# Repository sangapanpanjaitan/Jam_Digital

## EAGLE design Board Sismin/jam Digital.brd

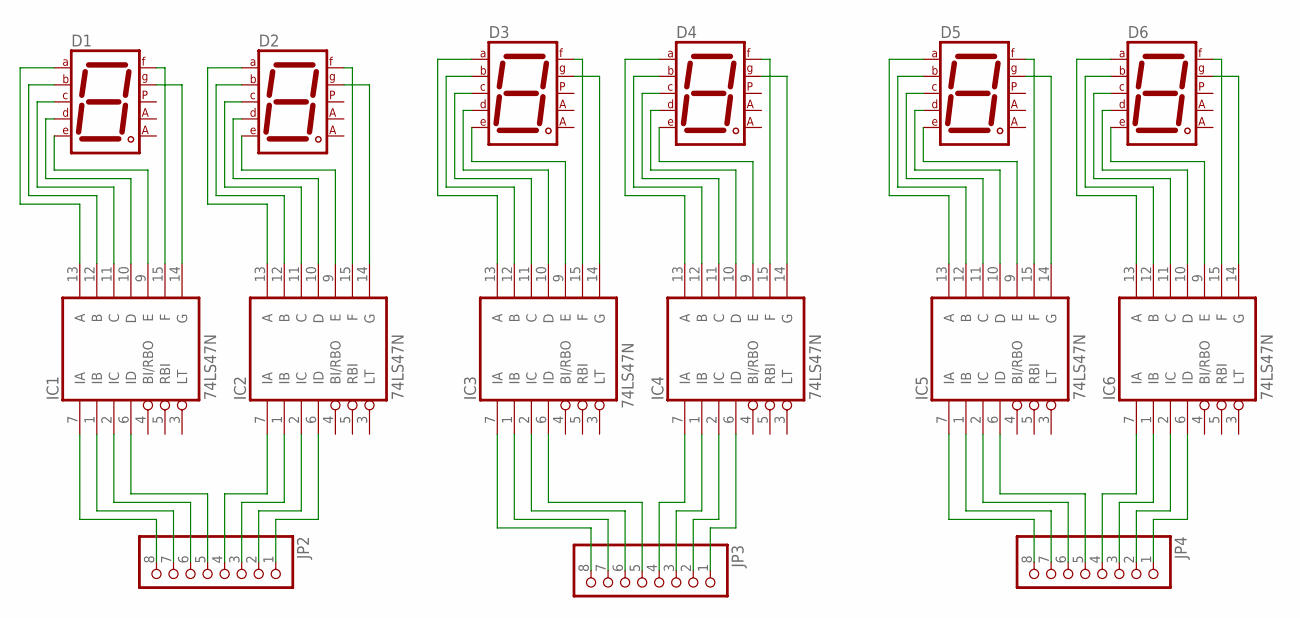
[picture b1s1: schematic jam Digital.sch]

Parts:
D1, D2, D3, D4, D5, D6: 7SEG-CA; 7SEG-13
IC1, IC2, IC3, IC4, IC5, IC6: 74LS47N; DIL16
JP2, JP3, JP4: PINHD-1X8; 1X08

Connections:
GND: IC1.8 (GND), IC2.8 (GND), IC3.8 (GND), IC4.8 (GND), IC5.8 (GND), IC6.8 (GND)
unnamed: D1.10 (G), IC1.14 (G)
unnamed: D2.10 (G), IC2.14 (G)
unnamed: D1.9 (F), IC1.15 (F)
unnamed: D2.9 (F), IC2.15 (F)
unnamed: D3.9 (F), IC3.15 (F)
unnamed: D3.10 (G), IC3.14 (G)
unnamed: D4.9 (F), IC4.15 (F)
unnamed: D4.10 (G), IC4.14 (G)
unnamed: D5.9 (F), IC5.15 (F)
unnamed: D5.10 (G), IC5.14 (G)
unnamed: D6.9 (F), IC6.15 (F)
unnamed: D6.10 (G), IC6.14 (G)
unnamed: D1.1 (E), IC1.9 (E)
unnamed: D1.2 (D), IC1.10 (D)
unnamed: D1.4 (C), IC1.11 (C)
unnamed: D1.6 (B), IC1.12 (B)
unnamed: D1.7 (A), IC1.13 (A)
unnamed: D2.1 (E), IC2.9 (E)
unnamed: D2.2 (D), IC2.10 (D)
unnamed: D2.4 (C), IC2.11 (C)
unnamed: D2.6 (B), IC2.12 (B)
unnamed: D2.7 (A), IC2.13 (A)
unnamed: D3.1 (E), IC3.9 (E)
unnamed: D3.2 (D), IC3.10 (D)
unnamed: D3.4 (C), IC3.11 (C)
unnamed: D3.6 (B), IC3.12 (B)
unnamed: D3.7 (A), IC3.13 (A)
unnamed: D4.1 (E), IC4.9 (E)
unnamed: D4.2 (D), IC4.10 (D)
unnamed: D4.4 (C), IC4.11 (C)
unnamed: D4.6 (B), IC4.12 (B)
unnamed: D4.7 (A), IC4.13 (A)
unnamed: D5.1 (E), IC5.9 (E)
unnamed: D5.2 (D), IC5.10 (D)
unnamed: D5.4 (C), IC5.11 (C)
unnamed: D5.6 (B), IC5.12 (B)
unnamed: D5.7 (A), IC5.13 (A)
unnamed: D6.1 (E), IC6.9 (E)
unnamed: D6.2 (D), IC6.10 (D)
unnamed: D6.4 (C), IC6.11 (C)
unnamed: D6.6 (B), IC6.12 (B)
unnamed: D6.7 (A), IC6.13 (A)
unnamed: IC1.7 (IA), JP2.8
unnamed: IC1.1 (IB), JP2.7
unnamed: IC1.2 (IC), JP2.6
unnamed: IC1.6 (ID), JP2.5
unnamed: IC2.7 (IA), JP2.4
unnamed: IC2.1 (IB), JP2.3
unnamed: IC2.2 (IC), JP2.2
unnamed: IC2.6 (ID), JP2.1
unnamed: IC3.7 (IA), JP3.8
unnamed: IC3.1 (IB), JP3.7
unnamed: IC3.2 (IC), JP3.6
unnamed: IC3.6 (ID), JP3.5
unnamed: IC4.7 (IA), JP3.4
unnamed: IC4.1 (IB), JP3.3
unnamed: IC4.2 (IC), JP3.2
unnamed: IC4.6 (ID), JP3.1
unnamed: IC5.7 (IA), JP4.8
unnamed: IC5.1 (IB), JP4.7
unnamed: IC5.2 (IC), JP4.6
unnamed: IC5.6 (ID), JP4.5
unnamed: IC6.7 (IA), JP4.4
unnamed: IC6.1 (IB), JP4.3
unnamed: IC6.2 (IC), JP4.2
unnamed: IC6.6 (ID), JP4.1
VCC: IC1.16 (VCC), IC2.16 (VCC), IC3.16 (VCC), IC4.16 (VCC), IC5.16 (VCC), IC6.16 (VCC)

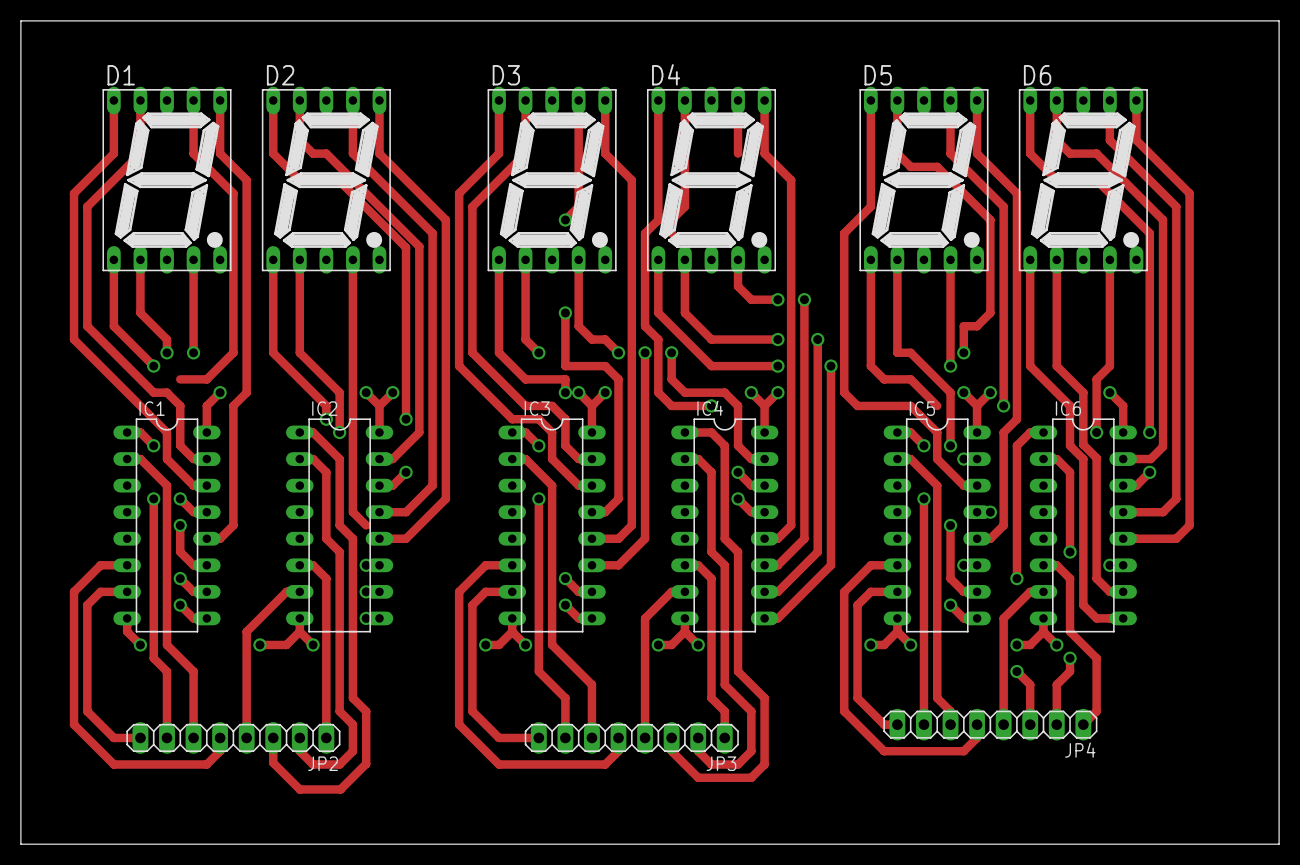
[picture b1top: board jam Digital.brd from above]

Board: 2 copper layers, 120.3 x 78.7 mm, 15 parts (0 on the bottom side), 68 nets.

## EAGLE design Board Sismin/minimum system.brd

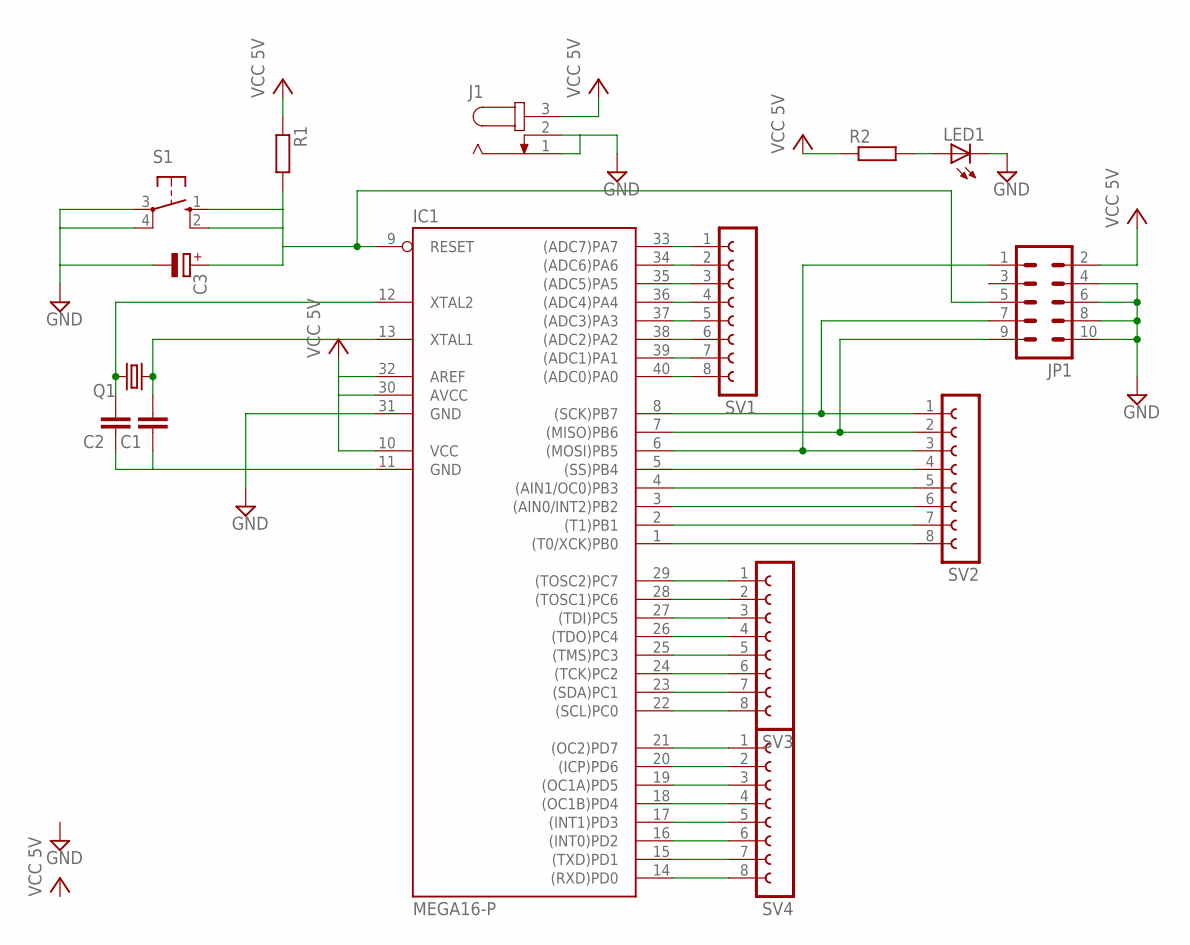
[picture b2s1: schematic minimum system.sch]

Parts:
C1, C2: C2.5/2; C2.5-2
C3: CPOL-EUE3.5-8; E3,5-8
IC1: MEGA16-P; DIL40
J1: JACK-PLUG0; SPC4077
JP1: ML10
LED1: LED5MM
Q1: CRYSTALHC49S; HC49/S
R1, R2: R-EU_0207/10; 0207/10
S1: 10-XX; B3F-10XX
SV1, SV2, SV3, SV4: FE08-1; FE08

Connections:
GND: C1.1, C2.1, C3.-, IC1.11 (GND), IC1.31 (GND), J1.1, J1.2, JP1.4, JP1.6, JP1.8, JP1.10, LED1.K (C), S1.3, S1.4 (P1)
unnamed: C2.2, IC1.12 (XTAL2), Q1.2
unnamed: C1.2, IC1.13 (XTAL1), Q1.1
unnamed: LED1.A, R2.2
unnamed: C3.+, R1.2, S1.1 (S), S1.2 (S1)
unnamed: IC1.9 (RESET), JP1.5
unnamed: IC1.29 ((TOSC2)PC7), SV3.1
unnamed: IC1.28 ((TOSC1)PC6), SV3.2
unnamed: IC1.27 ((TDI)PC5), SV3.3
unnamed: IC1.1 ((T0/XCK)PB0), SV2.8
unnamed: IC1.40 ((ADC0)PA0), SV1.8
unnamed: IC1.39 ((ADC1)PA1), SV1.7
unnamed: IC1.38 ((ADC2)PA2), SV1.6
unnamed: IC1.37 ((ADC3)PA3), SV1.5
unnamed: IC1.36 ((ADC4)PA4), SV1.4
unnamed: IC1.35 ((ADC5)PA5), SV1.3
unnamed: IC1.34 ((ADC6)PA6), SV1.2
unnamed: IC1.33 ((ADC7)PA7), SV1.1
unnamed: IC1.2 ((T1)PB1), SV2.7
unnamed: IC1.3 ((AIN0/INT2)PB2), SV2.6
unnamed: IC1.4 ((AIN1/OC0)PB3), SV2.5
unnamed: IC1.5 ((SS)PB4), SV2.4
unnamed: IC1.6 ((MOSI)PB5), JP1.1, SV2.3
unnamed: IC1.7 ((MISO)PB6), JP1.9, SV2.2
unnamed: IC1.8 ((SCK)PB7), JP1.7, SV2.1
unnamed: IC1.26 ((TDO)PC4), SV3.4
unnamed: IC1.25 ((TMS)PC3), SV3.5
unnamed: IC1.24 ((TCK)PC2), SV3.6
unnamed: IC1.23 ((SDA)PC1), SV3.7
unnamed: IC1.22 ((SCL)PC0), SV3.8
unnamed: IC1.21 ((OC2)PD7), SV4.1
unnamed: IC1.20 ((ICP)PD6), SV4.2
unnamed: IC1.19 ((OC1A)PD5), SV4.3
unnamed: IC1.18 ((OC1B)PD4), SV4.4
unnamed: IC1.17 ((INT1)PD3), SV4.5
unnamed: IC1.16 ((INT0)PD2), SV4.6
unnamed: IC1.15 ((TXD)PD1), SV4.7
unnamed: IC1.14 ((RXD)PD0), SV4.8
VCC: IC1.10 (VCC), IC1.30 (AVCC), IC1.32 (AREF), J1.3, JP1.2, R1.1, R2.1

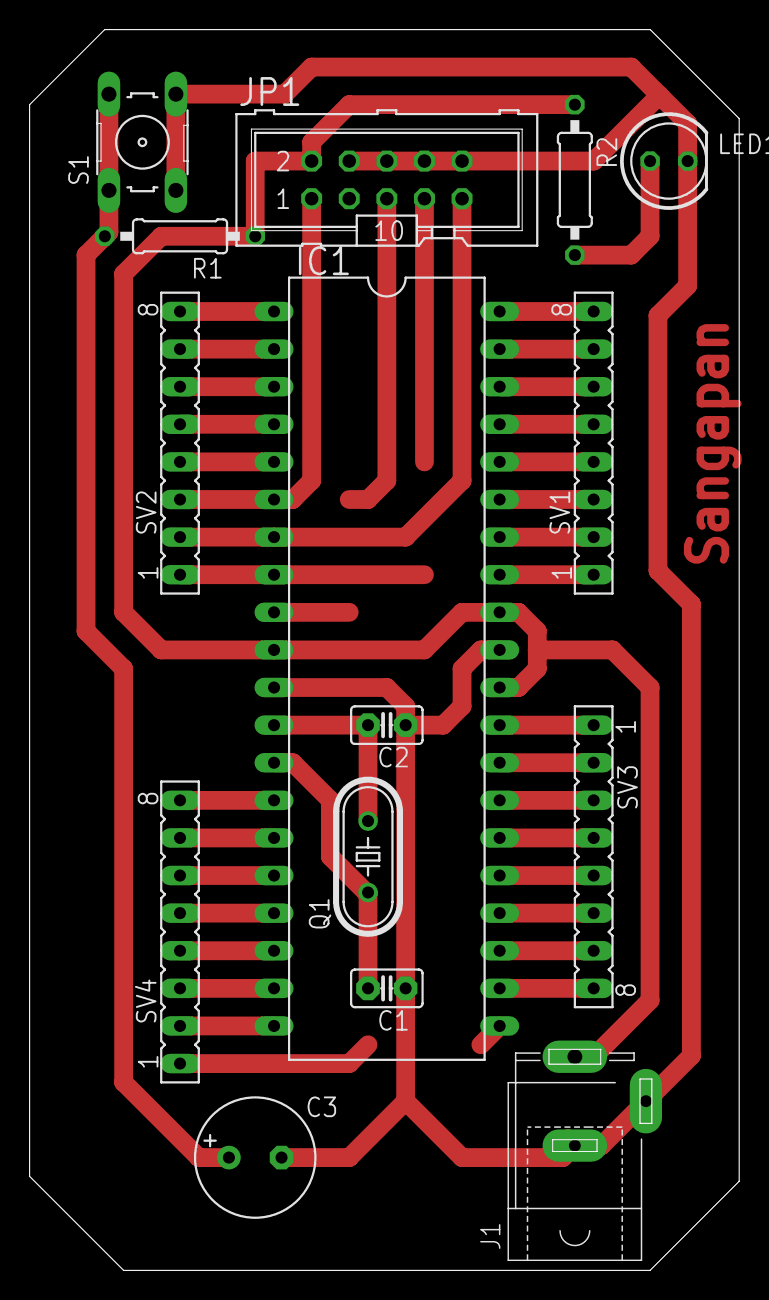
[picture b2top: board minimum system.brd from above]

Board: 2 copper layers, 47.9 x 83.8 mm, 15 parts (0 on the bottom side), 39 nets.

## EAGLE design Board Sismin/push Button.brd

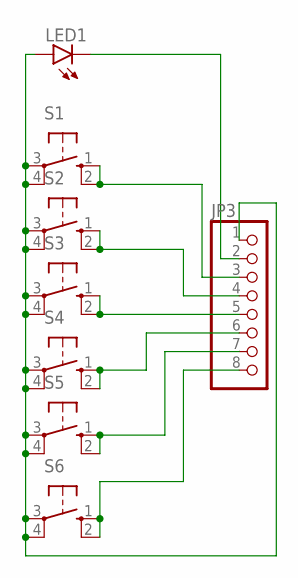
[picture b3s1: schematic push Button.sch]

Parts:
JP3: PINHD-1X8; 1X08
LED1: LED5MM
S1, S2, S3, S4, S5, S6: 10-XX; B3F-10XX

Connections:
unnamed: JP3.1, LED1.A, S1.3, S1.4 (P1), S2.3, S2.4 (P1), S3.3, S3.4 (P1), S4.3, S4.4 (P1), S5.3, S5.4 (P1), S6.3, S6.4 (P1)
unnamed: JP3.8, S6.1 (S), S6.2 (S1)
unnamed: JP3.7, S5.1 (S), S5.2 (S1)
unnamed: JP3.6, S4.1 (S), S4.2 (S1)
unnamed: JP3.5, S3.1 (S), S3.2 (S1)
unnamed: JP3.4, S2.1 (S), S2.2 (S1)
unnamed: JP3.3, S1.1 (S), S1.2 (S1)
unnamed: JP3.2, LED1.K (C)

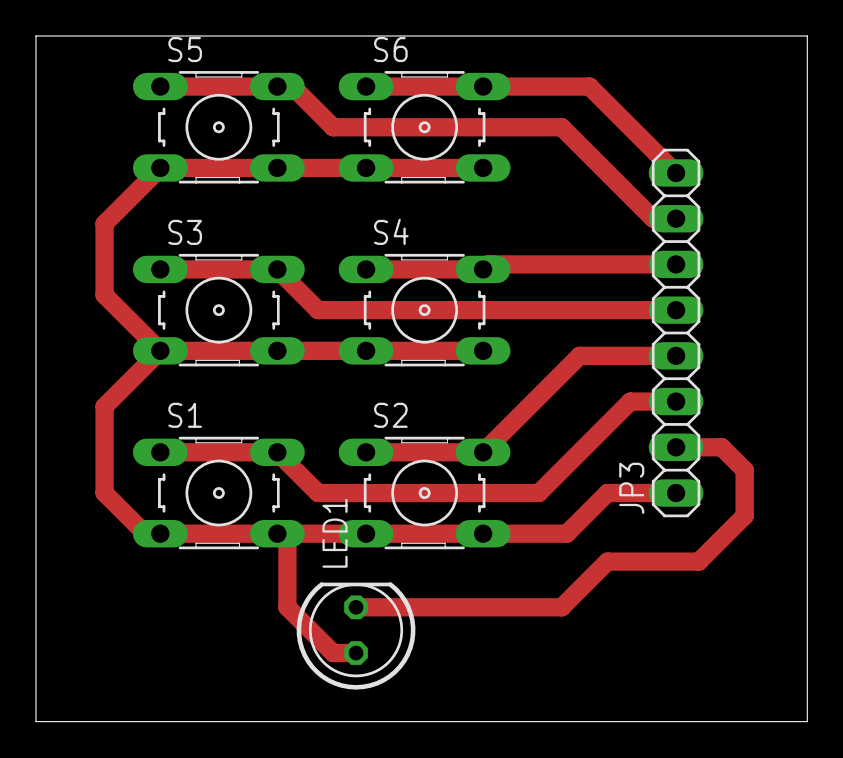
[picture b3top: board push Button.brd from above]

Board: 2 copper layers, 42.9 x 38.1 mm, 8 parts (0 on the bottom side), 8 nets.

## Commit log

2023-11-24 Commit awal
